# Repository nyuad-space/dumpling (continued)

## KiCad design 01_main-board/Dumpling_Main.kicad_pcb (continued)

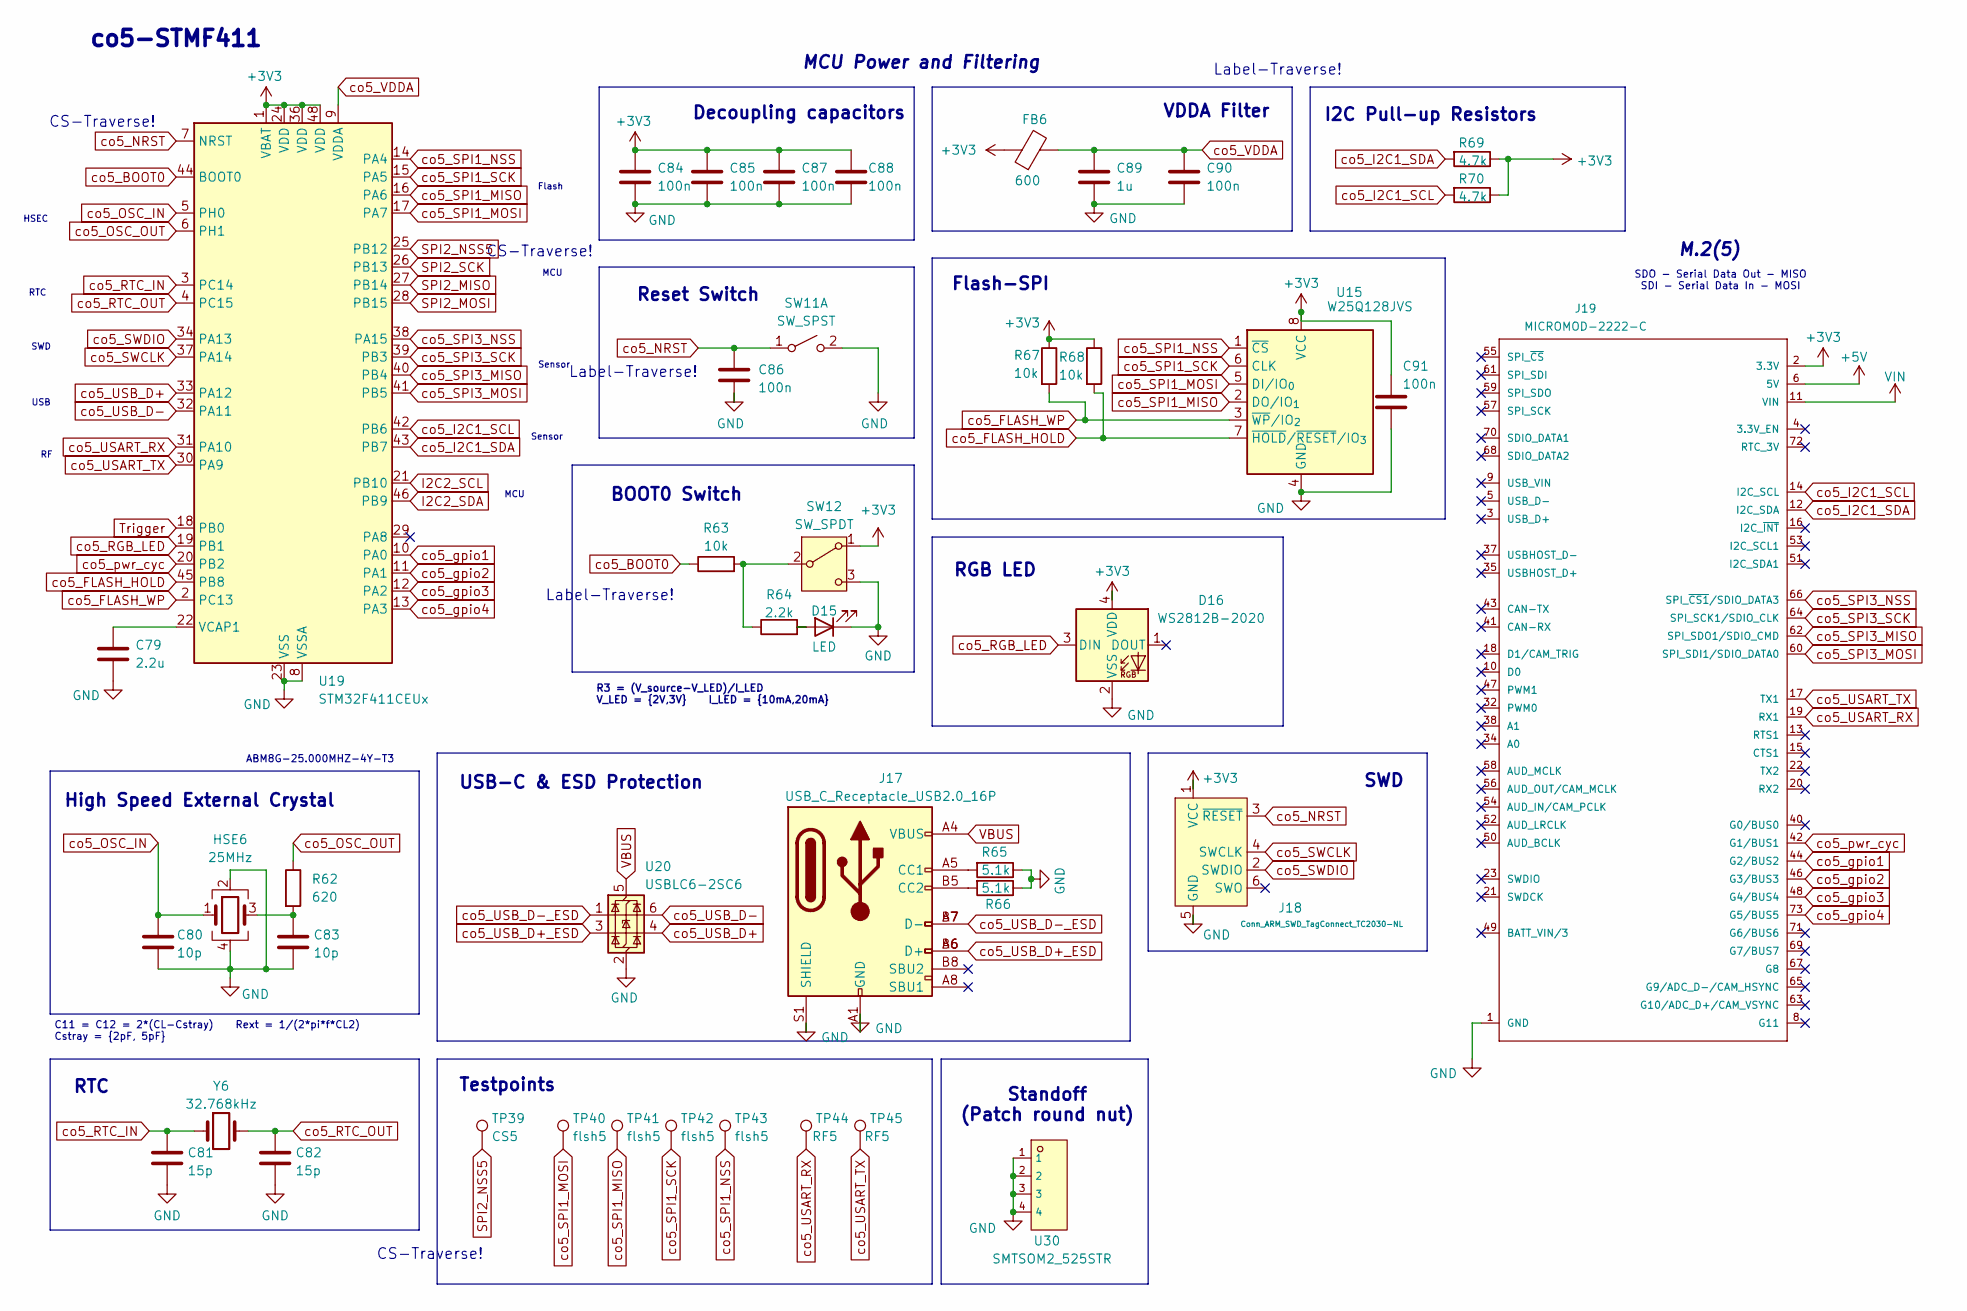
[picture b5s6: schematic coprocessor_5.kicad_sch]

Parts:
C79: 2.2u; C_0603_1608Metric
C80, C83: 10p; C_0402_1005Metric
C81, C82: 15p; C_0402_1005Metric
C84, C85, C86, C87, C88, C90, C91: 100n; C_0402_1005Metric
C89: 1u; C_0603_1608Metric
D15: LED; LED_0603_1608Metric
D16: WS2812B-2020; LED_WS2812B-2020_PLCC4_2.0x2.0mm
FB6: 600; L_0402_1005Metric
HSE6: 25MHz; Crystal_SMD_Abracon_ABM8G-4Pin_3.2x2.5mm
J17: USB_C_Receptacle_USB2.0_16P; USB_C_Receptacle_G-Switch_GT-USB-7051x
J18: Conn_ARM_SWD_TagConnect_TC2030-NL; Tag-Connect_TC2030-IDC-NL_2x03_P1.27mm_Vertical
J19: MICROMOD-2222-C; TE_2199119-4
R62: 620; R_0402_1005Metric
R63, R67, R68: 10k; R_0402_1005Metric
R64: 2.2k; R_0603_1608Metric
R65, R66: 5.1k; R_0402_1005Metric
R69, R70: 4.7k; R_0402_1005Metric
SW11: SW_SPST; SW_SPST_B3U-1000P
SW12: SW_SPDT; SW_JS102011JCQN
TP39: CS5; TestPoint_Pad_D1.0mm
TP40, TP41, TP42, TP43: flsh5; TestPoint_Pad_D1.0mm
TP44, TP45: RF5; TestPoint_Pad_D1.0mm
U15: W25Q128JVS; SOIC-8_5.3x5.3mm_P1.27mm
U19: STM32F411CEUx; QFN-48-1EP_7x7mm_P0.5mm_EP5.6x5.6mm
U20: USBLC6-2SC6; SOT-23-6
U30: SMTSOM2_525STR; SMD_BD5.6-D4.1; LCSC C22368605
Y6: 32.768kHz; Crystal_SMD_3215-2Pin_3.2x1.5mm

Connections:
+5V: J19.6 (5V); also elsewhere on the board
I2C2_SCL: U19.21 (PB10); also elsewhere on the board
I2C2_SDA: U19.46 (PB9); also elsewhere on the board
unnamed: C83.1, HSE6.3, R62.2
unnamed: D15.2 (A), R64.2
unnamed: J17.A5 (CC1), R65.2
unnamed: J17.B5 (CC2), R66.2
unnamed: R63.2, R64.1, SW12.2 (B)
unnamed: C79.1, U19.22 (VCAP1)
SPI2_MISO: U19.27 (PB14); also elsewhere on the board
SPI2_MOSI: U19.28 (PB15); also elsewhere on the board
SPI2_NSS5: TP39.1, U19.25 (PB12); also elsewhere on the board
SPI2_SCK: U19.26 (PB13); also elsewhere on the board
Trigger: U19.18 (PB0); also elsewhere on the board
VBUS: J17.A4 (VBUS), J17.A9 (VBUS), J17.B4 (VBUS), J17.B9 (VBUS), U20.5 (VBUS); also elsewhere on the board
VIN: J19.11 (VIN); also elsewhere on the board
co5_BOOT0: R63.1, U19.44 (BOOT0)
co5_FLASH_HOLD: R68.2, U15.7 (~HOLD/~RESET/IO_{3}), U19.45 (PB8)
co5_FLASH_WP: R67.2, U15.3 (~WP/IO_{2}), U19.2 (PC13)
co5_I2C1_SCL: J19.14 (I2C_SCL), R70.2, U19.42 (PB6)
co5_I2C1_SDA: J19.12 (I2C_SDA), R69.2, U19.43 (PB7)
co5_NRST: C86.1, J18.3 (~RESET), SW11.1 (A), U19.7 (NRST); also elsewhere on the board
co5_OSC_IN: C80.1, HSE6.1, U19.5 (PH0)
co5_OSC_OUT: R62.1, U19.6 (PH1)
co5_RGB_LED: D16.3 (DIN), U19.19 (PB1)
co5_RTC_IN: C81.1, U19.3 (PC14), Y6.1
co5_RTC_OUT: C82.1, U19.4 (PC15), Y6.2
co5_SPI1_MISO: TP41.1, U15.2 (DO/IO_{1}), U19.16 (PA6)
co5_SPI1_MOSI: TP40.1, U15.5 (DI/IO_{0}), U19.17 (PA7)
co5_SPI1_NSS: TP43.1, U15.1 (~CS), U19.14 (PA4)
co5_SPI1_SCK: TP42.1, U15.6 (CLK), U19.15 (PA5)
co5_SPI3_MISO: J19.62 (SPI_SDO1/SDIO_CMD), U19.40 (PB4)
co5_SPI3_MOSI: J19.60 (SPI_SDI1/SDIO_DATA0), U19.41 (PB5)
co5_SPI3_NSS: J19.66 (SPI_~CS1/SDIO_DATA3), U19.38 (PA15)
co5_SPI3_SCK: J19.64 (SPI_SCK1/SDIO_CLK), U19.39 (PB3)
co5_SWCLK: J18.4 (SWCLK), U19.37 (PA14)
co5_SWDIO: J18.2 (SWDIO), U19.34 (PA13)
co5_USART_RX: J19.19 (RX1), TP44.1, U19.31 (PA10)
co5_USART_TX: J19.17 (TX1), TP45.1, U19.30 (PA9)
co5_USB_D+: U19.33 (PA12), U20.4 (I/O2)
co5_USB_D+_ESD: J17.A6 (D+), J17.B6 (D+), U20.3 (I/O2)
co5_USB_D-: U19.32 (PA11), U20.6 (I/O1)
co5_USB_D-_ESD: J17.A7 (D-), J17.B7 (D-), U20.1 (I/O1)
co5_VDDA: C89.1, C90.1, FB6.2, U19.9 (VDDA)
co5_gpio1: J19.44 (G2/BUS2), U19.10 (PA0)
co5_gpio2: J19.46 (G3/BUS3), U19.11 (PA1)
co5_gpio3: J19.48 (G4/BUS4), U19.12 (PA2)
co5_gpio4: J19.73 (G5/BUS5), U19.13 (PA3)
co5_pwr_cyc: J19.42 (G1/BUS1), U19.20 (PB2)

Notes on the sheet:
USB
Flash
Reset Switch
M.2(5)
Testpoints
BOOT0 Switch
R3 = (V_source-V_LED)/I_LED V_LED = {2V,3V} I_LED = {10mA,20mA}
SDO - Serial Data Out - MISO SDI - Serial Data In - MOSI
RTC
Sensor
CS-Traverse!
MCU Power and Filtering
MCU
ABM8G-25.000MHZ-4Y-T3
SWD
RGB LED
Flash-SPI
co5-STMF411
Standoff (Patch round nut)
SWD
I2C Pull-up Resistors
Label-Traverse!
VDDA Filter
RTC
C11 = C12 = 2*(CL-Cstray) Rext = 1/(2*pi*f*CL2) Cstray = {2pF, 5pF}
High Speed External Crystal
Decoupling capacitors
USB-C & ESD Protection
HSEC

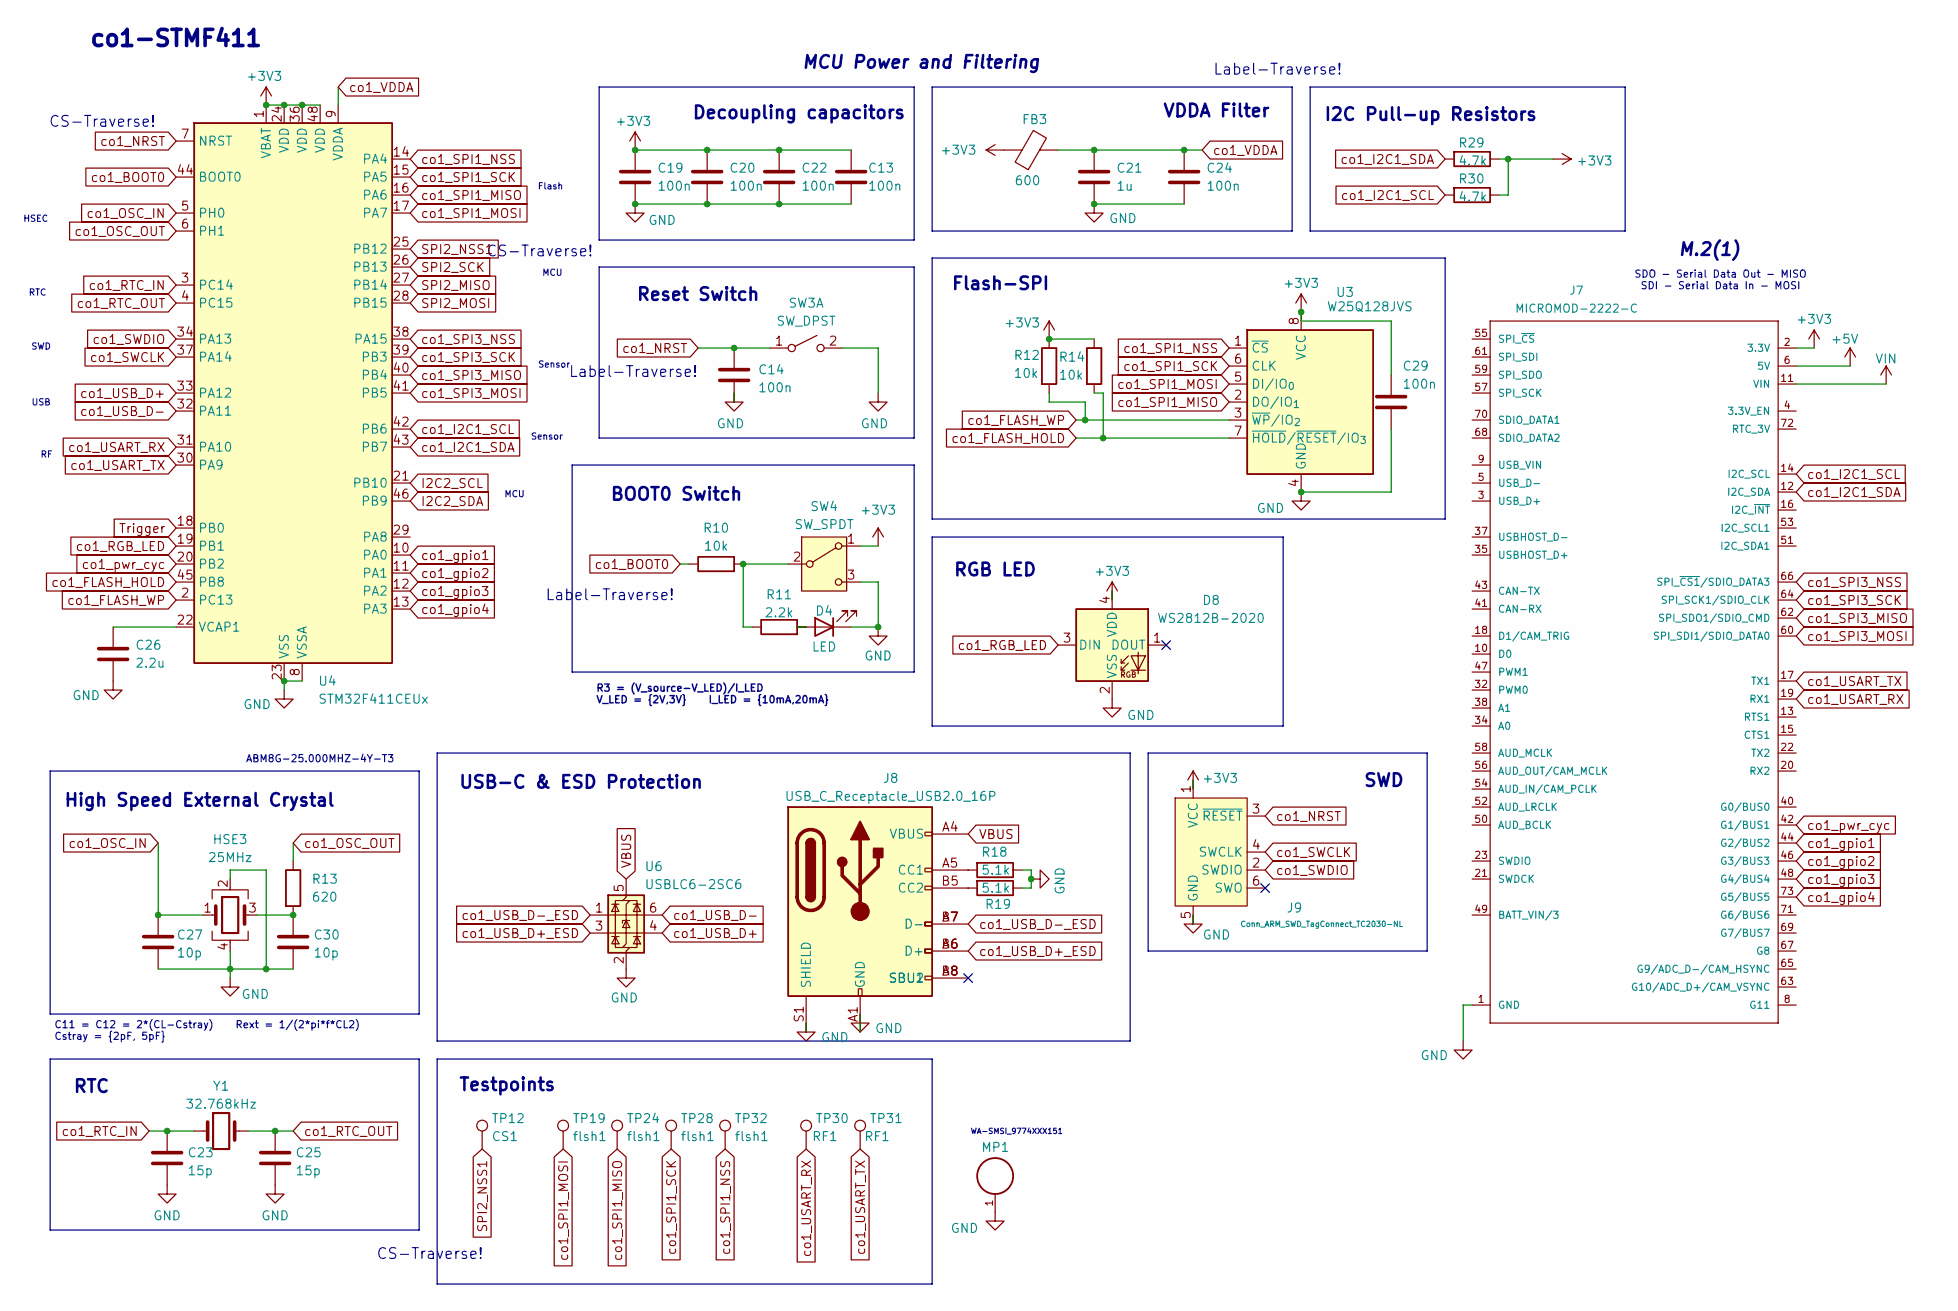
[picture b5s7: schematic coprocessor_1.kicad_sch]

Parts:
C13, C14, C19, C20, C22, C24, C29: 100n; C_0402_1005Metric
C21: 1u; C_0603_1608Metric
C23, C25: 15p; C_0402_1005Metric
C26: 2.2u; C_0603_1608Metric
C27, C30: 10p; C_0402_1005Metric
D4: LED; LED_0603_1608Metric
D8: WS2812B-2020; LED_WS2812B-2020_PLCC4_2.0x2.0mm
FB3: 600; L_0402_1005Metric
HSE3: 25MHz; Crystal_SMD_Abracon_ABM8G-4Pin_3.2x2.5mm
J7: MICROMOD-2222-C; TE_2199119-4
J8: USB_C_Receptacle_USB2.0_16P; USB_C_Receptacle_G-Switch_GT-USB-7051x
J9: Conn_ARM_SWD_TagConnect_TC2030-NL; Tag-Connect_TC2030-IDC-NL_2x03_P1.27mm_Vertical
MP1: WA-SMSI_9774025151; PART-NUMBER 9774025151R
R10, R12, R14: 10k; R_0402_1005Metric
R11: 2.2k; R_0603_1608Metric
R13: 620; R_0402_1005Metric
R18, R19: 5.1k; R_0402_1005Metric
R29, R30: 4.7k; R_0402_1005Metric
SW3: SW_DPST; SW_SPST_B3U-1000P
SW4: SW_SPDT; SW_CJS-1200TA
TP12: CS1; TestPoint_Pad_D1.0mm
TP19, TP24, TP28, TP32: flsh1; TestPoint_Pad_D1.0mm
TP30, TP31: RF1; TestPoint_Pad_D1.0mm
U3: W25Q128JVS; SOIC-8_5.3x5.3mm_P1.27mm
U4: STM32F411CEUx; QFN-48-1EP_7x7mm_P0.5mm_EP5.6x5.6mm
U6: USBLC6-2SC6; SOT-23-6
Y1: 32.768kHz; Crystal_SMD_3215-2Pin_3.2x1.5mm

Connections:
+5V: J7.6 (5V); also elsewhere on the board
I2C2_SCL: U4.21 (PB10); also elsewhere on the board
I2C2_SDA: U4.46 (PB9); also elsewhere on the board
unnamed: C30.1, HSE3.3, R13.2
unnamed: D4.2 (A), R11.2
unnamed: J8.A5 (CC1), R18.2
unnamed: J8.B5 (CC2), R19.2
unnamed: R10.2, R11.1, SW4.2 (B)
unnamed: C26.1, U4.22 (VCAP1)
SPI2_MISO: U4.27 (PB14); also elsewhere on the board
SPI2_MOSI: U4.28 (PB15); also elsewhere on the board
SPI2_NSS1: TP12.1, U4.25 (PB12); also elsewhere on the board
SPI2_SCK: U4.26 (PB13); also elsewhere on the board
Trigger: U4.18 (PB0); also elsewhere on the board
VBUS: J8.A4 (VBUS), J8.A9 (VBUS), J8.B4 (VBUS), J8.B9 (VBUS), U6.5 (VBUS); also elsewhere on the board
VIN: J7.11 (VIN); also elsewhere on the board
co1_BOOT0: R10.1, U4.44 (BOOT0)
co1_FLASH_HOLD: R14.2, U3.7 (~HOLD/~RESET/IO_{3}), U4.45 (PB8)
co1_FLASH_WP: R12.2, U3.3 (~WP/IO_{2}), U4.2 (PC13)
co1_I2C1_SCL: J7.14 (I2C_SCL), R30.2, U4.42 (PB6)
co1_I2C1_SDA: J7.12 (I2C_SDA), R29.2, U4.43 (PB7)
co1_NRST: C14.1, J9.3 (~RESET), SW3.1 (A), U4.7 (NRST); also elsewhere on the board
co1_OSC_IN: C27.1, HSE3.1, U4.5 (PH0)
co1_OSC_OUT: R13.1, U4.6 (PH1)
co1_RGB_LED: D8.3 (DIN), U4.19 (PB1)
co1_RTC_IN: C23.1, U4.3 (PC14), Y1.1
co1_RTC_OUT: C25.1, U4.4 (PC15), Y1.2
co1_SPI1_MISO: TP24.1, U3.2 (DO/IO_{1}), U4.16 (PA6)
co1_SPI1_MOSI: TP19.1, U3.5 (DI/IO_{0}), U4.17 (PA7)
co1_SPI1_NSS: TP32.1, U3.1 (~CS), U4.14 (PA4)
co1_SPI1_SCK: TP28.1, U3.6 (CLK), U4.15 (PA5)
co1_SPI3_MISO: J7.62 (SPI_SDO1/SDIO_CMD), U4.40 (PB4)
co1_SPI3_MOSI: J7.60 (SPI_SDI1/SDIO_DATA0), U4.41 (PB5)
co1_SPI3_NSS: J7.66 (SPI_~CS1/SDIO_DATA3), U4.38 (PA15)
co1_SPI3_SCK: J7.64 (SPI_SCK1/SDIO_CLK), U4.39 (PB3)
co1_SWCLK: J9.4 (SWCLK), U4.37 (PA14)
co1_SWDIO: J9.2 (SWDIO), U4.34 (PA13)
co1_USART_RX: J7.19 (RX1), TP30.1, U4.31 (PA10)
co1_USART_TX: J7.17 (TX1), TP31.1, U4.30 (PA9)
co1_USB_D+: U4.33 (PA12), U6.4 (I/O2)
co1_USB_D+_ESD: J8.A6 (D+), J8.B6 (D+), U6.3 (I/O2)
co1_USB_D-: U4.32 (PA11), U6.6 (I/O1)
co1_USB_D-_ESD: J8.A7 (D-), J8.B7 (D-), U6.1 (I/O1)
co1_VDDA: C21.1, C24.1, FB3.2, U4.9 (VDDA)
co1_gpio1: J7.44 (G2/BUS2), U4.10 (PA0)
co1_gpio2: J7.46 (G3/BUS3), U4.11 (PA1)
co1_gpio3: J7.48 (G4/BUS4), U4.12 (PA2)
co1_gpio4: J7.73 (G5/BUS5), U4.13 (PA3)
co1_pwr_cyc: J7.42 (G1/BUS1), U4.20 (PB2)

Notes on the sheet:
WA-SMSI_9774XXX151
Flash-SPI
VDDA Filter
I2C Pull-up Resistors
SDO - Serial Data Out - MISO SDI - Serial Data In - MOSI
Sensor
HSEC
ABM8G-25.000MHZ-4Y-T3
Testpoints
CS-Traverse!
RGB LED
M.2(1)
RTC
SWD
C11 = C12 = 2*(CL-Cstray) Rext = 1/(2*pi*f*CL2) Cstray = {2pF, 5pF}
RTC
co1-STMF411
USB
Reset Switch
Label-Traverse!
Flash
Decoupling capacitors
SWD
MCU
BOOT0 Switch
MCU Power and Filtering
R3 = (V_source-V_LED)/I_LED V_LED = {2V,3V} I_LED = {10mA,20mA}
USB-C & ESD Protection
High Speed External Crystal

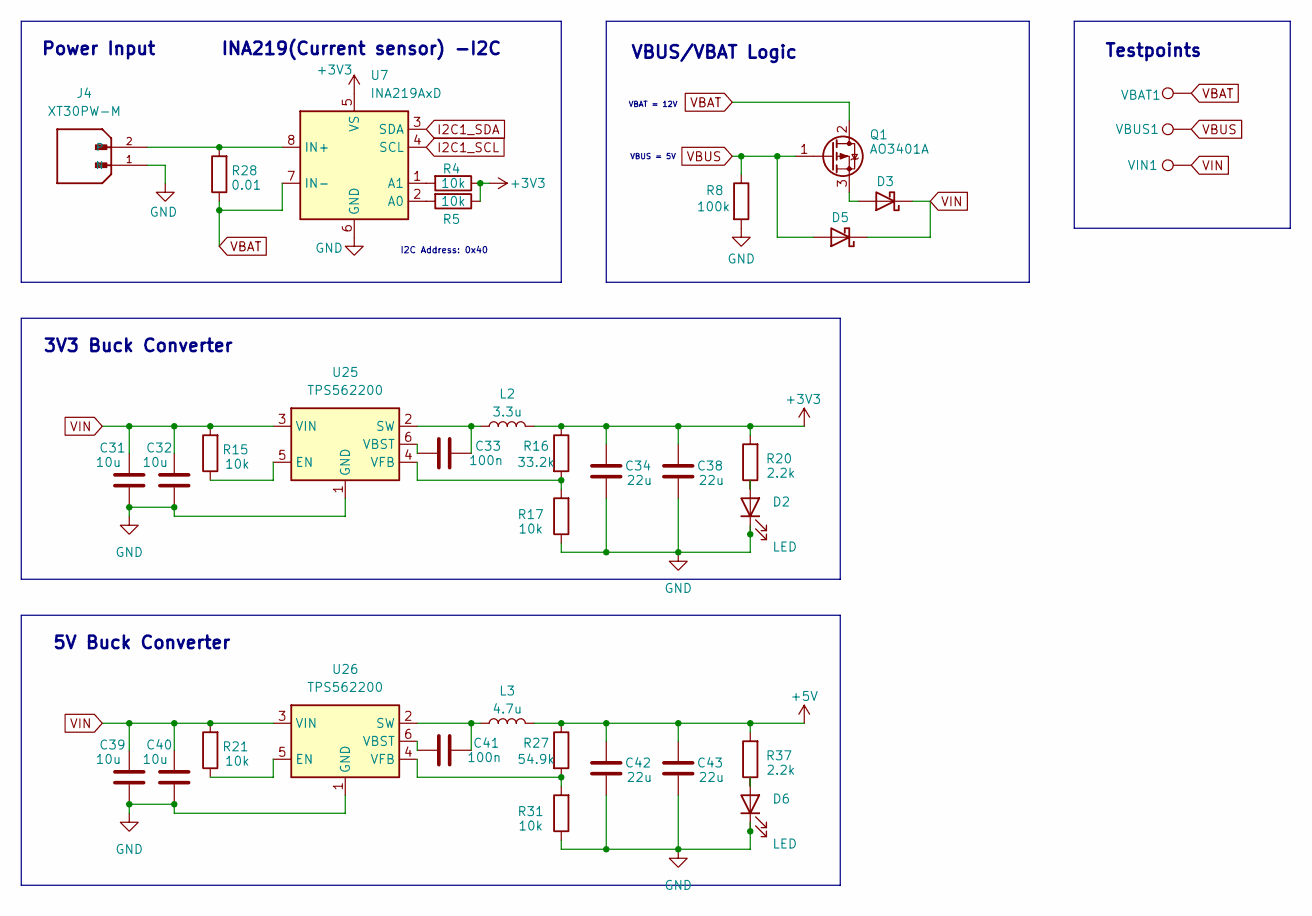
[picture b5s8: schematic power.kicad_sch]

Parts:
C31, C32, C39, C40: 10u; C_0805_2012Metric
C33, C41: 100n; C_0402_1005Metric
C34, C38, C42, C43: 22u; C_0805_2012Metric
D2, D6: LED; LED_0603_1608Metric
D3, D5: D_Schottky; D_SOD-323
J4: XT30PW-M; AMASS_XT30PW-M_1x02_P2.50mm_Horizontal; PARTREV 1.2
L2: 3.3u; L_Changjiang_FNR4030S
L3: 4.7u; L_Changjiang_FNR4030S
Q1: AO3401A; SOT-23
R4, R5, R15, R17, R21, R31: 10k; R_0402_1005Metric
R8: 100k; R_0603_1608Metric
R16: 33.2k; R_0402_1005Metric
R20, R37: 2.2k; R_0603_1608Metric
R27: 54.9k; R_0402_1005Metric
R28: 0.01; R_2512_6332Metric
U7: INA219AxD; SOIC-8_3.9x4.9mm_P1.27mm
U25, U26: TPS562200; SOT-23-6_Handsoldering
VBAT1: TestPoint; TestPoint_Pad_D1.5mm
VBUS1: TestPoint; TestPoint_Pad_D1.5mm
VIN1: TestPoint; TestPoint_Pad_D1.5mm

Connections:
+5V: C42.1, C43.1, L3.2, R27.1, R37.2; also elsewhere on the board
unnamed: D2.2 (A), R20.1
unnamed: D3.2 (A), Q1.3 (S)
unnamed: D6.2 (A), R37.1
unnamed 58: R5.2, U7.2 (A0); also elsewhere on the board
unnamed: R15.1, U25.5 (EN)
unnamed: C33.2, L2.1, U25.2 (SW)
unnamed: C33.1, U25.6 (VBST)
unnamed: R16.2, R17.2, U25.4 (VFB)
unnamed: R21.1, U26.5 (EN)
unnamed: C41.2, L3.1, U26.2 (SW)
unnamed: C41.1, U26.6 (VBST)
unnamed: R27.2, R31.2, U26.4 (VFB)
VBUS: D5.2 (A), Q1.1 (G), R8.1, VBUS1.1; also elsewhere on the board
VIN: C31.1, C32.1, C39.1, C40.1, D3.1 (K), D5.1 (K), R15.2, R21.2, U25.3 (VIN), U26.3 (VIN), VIN1.1; also elsewhere on the board

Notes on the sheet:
3V3 Buck Converter
VBAT = 12V
Testpoints
Power Input
5V Buck Converter
INA219(Current sensor) -I2C
VBUS/VBAT Logic
I2C Address: 0x40
VBUS = 5V

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
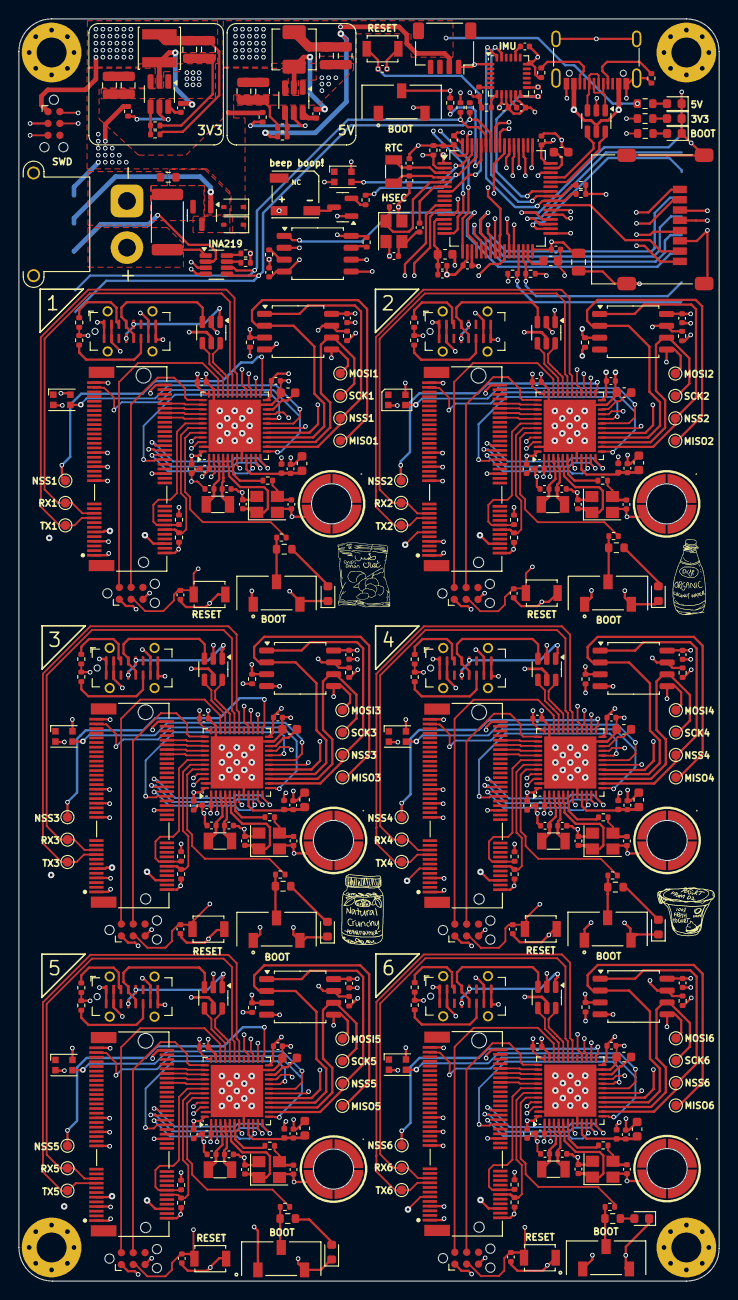
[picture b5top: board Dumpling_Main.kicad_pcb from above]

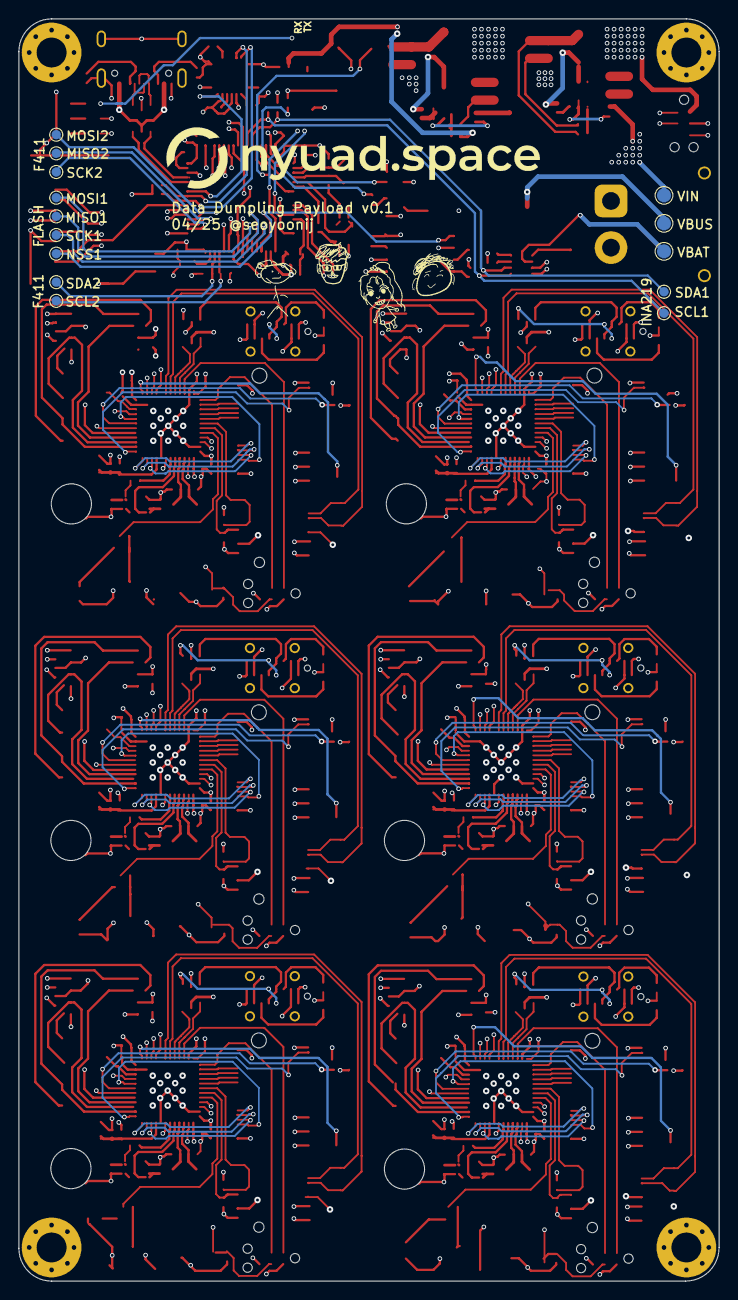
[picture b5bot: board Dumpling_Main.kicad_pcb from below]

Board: 6 copper layers, 75.0 x 135.2 mm, 363 parts (14 on the bottom side), 313 nets.

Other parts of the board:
U9: INA219AxDCN; SOT-23-8
U21, U29: SMTSOM2_525STR; SMD_BD5.6-D4.1

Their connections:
I2C1_SCL: U9.5 (SCL); also elsewhere on the board
I2C1_SDA: U9.6 (SDA); also elsewhere on the board
unnamed 58: U9.7 (A0); also elsewhere on the board

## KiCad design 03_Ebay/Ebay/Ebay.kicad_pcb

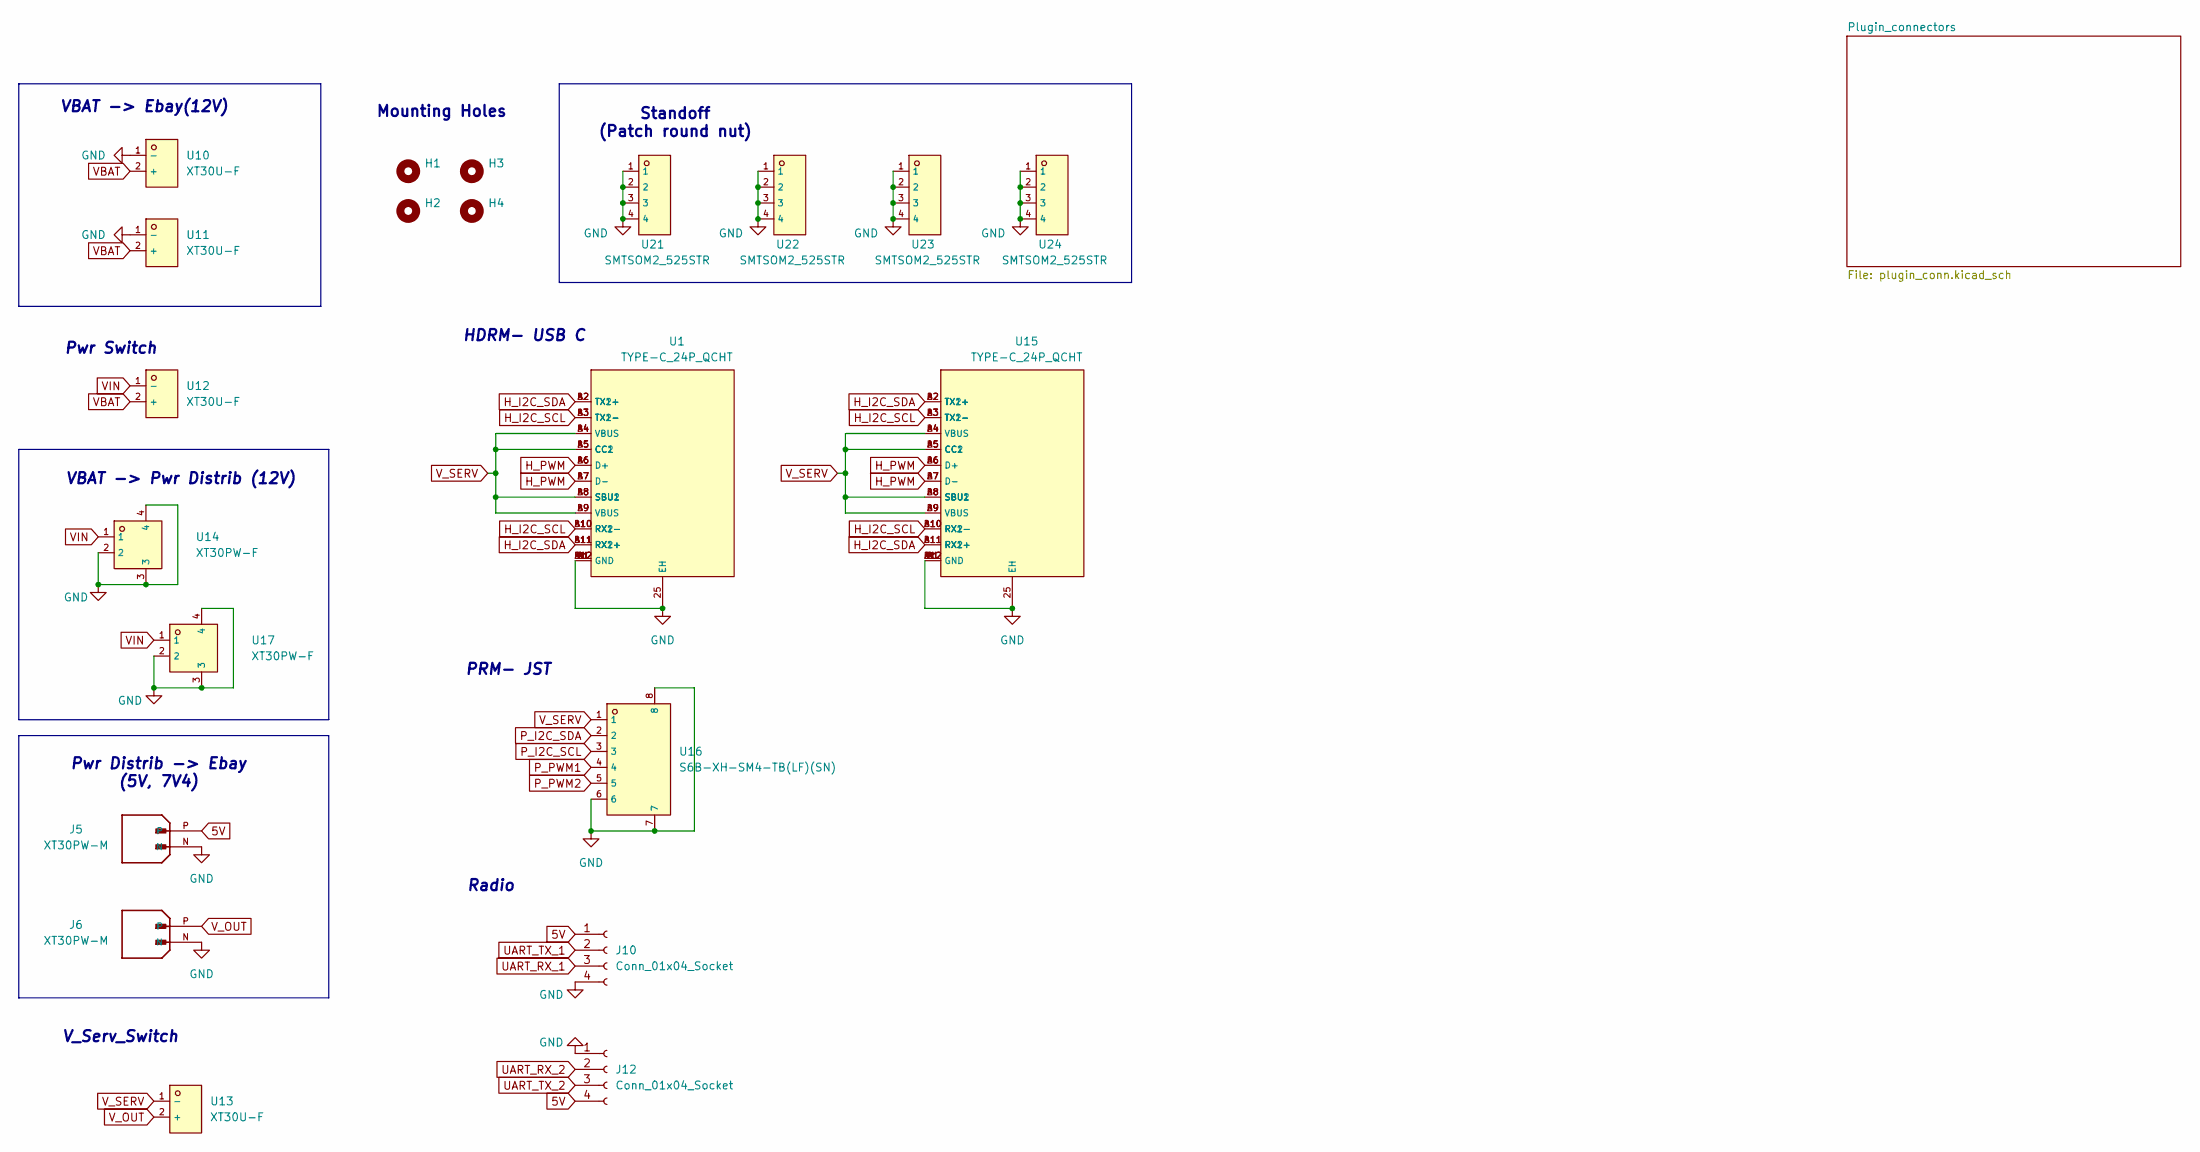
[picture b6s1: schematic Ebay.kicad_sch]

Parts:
H1, H2, H3, H4: MountingHole; MountingHole_3.2mm_M3_Pad_Via
J5, J6: XT30PW-M; AMASS_XT30PW-M; PARTREV 1.2
J10, J12: Conn_01x04_Socket; PinHeader_1x04_P2.54mm_Horizontal
U1, U15: TYPE-C_24P_QCHT; TYPE-C-SMD_TYPE-C-24P-QCHT; LCSC C456013
U10, U11, U12, U13: XT30U-F; CONN-TH_XT30U-F; LCSC C99102
U14, U17: XT30PW-F; CONN-TH_XT30PW-F-1; LCSC C2913282
U16: S6B-XH-SM4-TB(LF)(SN); CONN-SMD_S6B-XH-SM4-TB-LF-SN; LCSC C191914
U21, U22, U23, U24: SMTSOM2_525STR; SMD_BD5.6-D4.1; LCSC C22368605

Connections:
5V: J5.P, J10.1, J12.4; also elsewhere on the board
GND: J5.N, J6.N, J10.4, J12.1, U1.25 (EH), U1.A1 (GND), U1.A12 (GND), U1.B1 (GND), U1.B12 (GND), U10.1 (-), U11.1 (-), U14.2, U14.3, U14.4, U15.25 (EH), U15.A1 (GND), U15.A12 (GND), U15.B1 (GND), U15.B12 (GND), U16.6, U16.7, U16.8, U17.2, U17.3, U17.4, U21.1, U21.2, U21.3, U21.4, U22.1, U22.2, U22.3, U22.4, U23.1, U23.2, U23.3, U23.4, U24.1, U24.2, U24.3, U24.4; also elsewhere on the board
H_I2C_SCL: U1.A3 (TX1-), U1.A10 (RX2-), U1.B3 (TX2-), U1.B10 (RX1-), U15.A3 (TX1-), U15.A10 (RX2-), U15.B3 (TX2-), U15.B10 (RX1-); also elsewhere on the board
H_I2C_SDA: U1.A2 (TX1+), U1.A11 (RX2+), U1.B2 (TX2+), U1.B11 (RX1+), U15.A2 (TX1+), U15.A11 (RX2+), U15.B2 (TX2+), U15.B11 (RX1+); also elsewhere on the board
H_PWM: U1.A6 (D+), U1.A7 (D-), U1.B6 (D+), U1.B7 (D-), U15.A6 (D+), U15.A7 (D-), U15.B6 (D+), U15.B7 (D-); also elsewhere on the board
P_I2C_SCL: U16.3; also elsewhere on the board
P_I2C_SDA: U16.2; also elsewhere on the board
P_PWM1: U16.4; also elsewhere on the board
P_PWM2: U16.5; also elsewhere on the board
UART_RX_1: J10.3; also elsewhere on the board
UART_RX_2: J12.2; also elsewhere on the board
UART_TX_1: J10.2; also elsewhere on the board
UART_TX_2: J12.3; also elsewhere on the board
VBAT: U10.2 (+), U11.2 (+), U12.2 (+)
VIN: U12.1 (-), U14.1, U17.1
V_OUT: J6.P, U13.2 (+)

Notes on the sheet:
PRM- JST
VBAT -> Pwr Distrib (12V)
Pwr Switch
Radio
Pwr Distrib -> Ebay (5V, 7V4)
VBAT -> Ebay(12V)
V_Serv_Switch
Standoff (Patch round nut)
Mounting Holes
HDRM- USB C

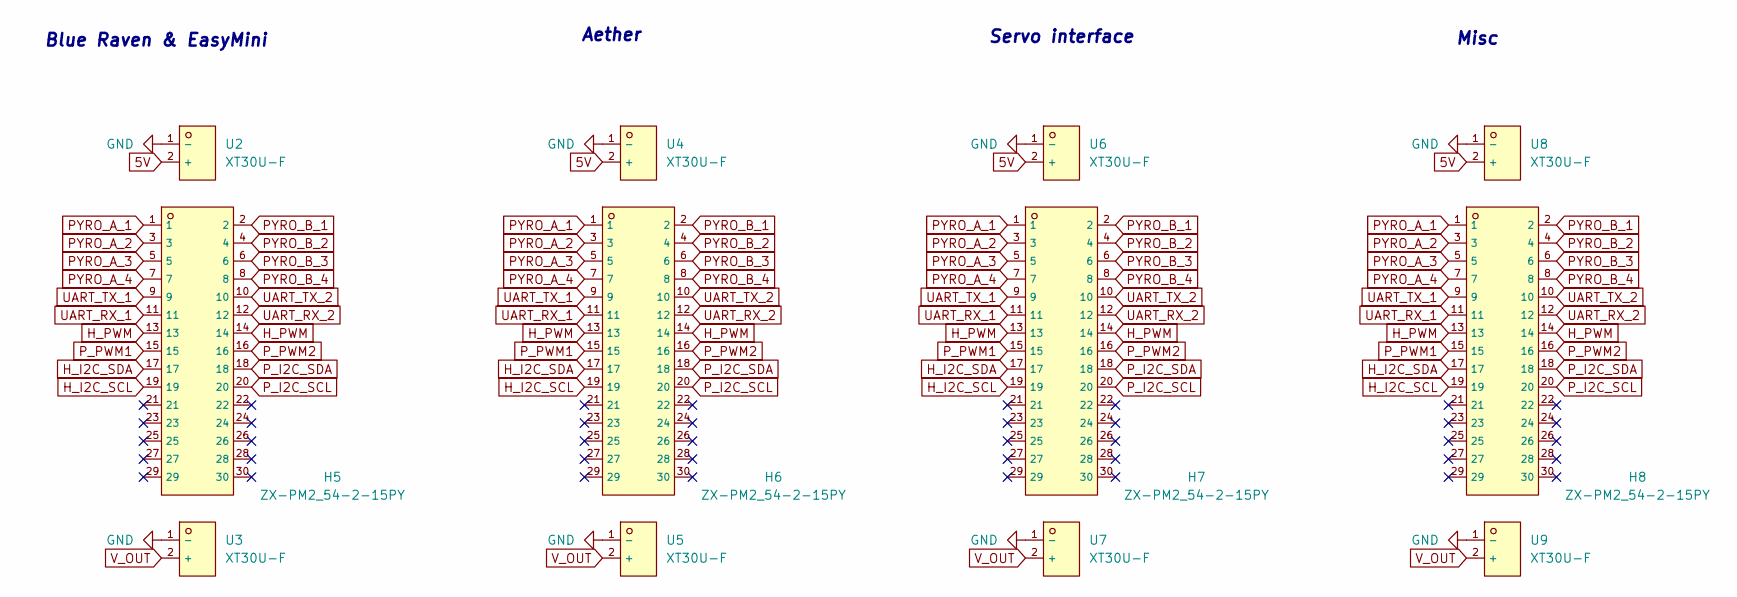
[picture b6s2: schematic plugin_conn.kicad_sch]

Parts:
H5, H6, H7, H8: ZX-PM2_54-2-15PY; PinSocket_2x15_P2.54mm_Vertical; LCSC C7499350
U2, U3, U4, U5, U6, U7, U8, U9: XT30U-F; CONN-TH_XT30U-F; LCSC C99102

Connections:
5V: U2.2 (+), U4.2 (+), U6.2 (+), U8.2 (+); also elsewhere on the board
GND: U2.1 (-), U3.1 (-), U4.1 (-), U5.1 (-), U6.1 (-), U7.1 (-), U8.1 (-), U9.1 (-); also elsewhere on the board
H_I2C_SCL: H5.19, H6.19, H7.19, H8.19; also elsewhere on the board
H_I2C_SDA: H5.17, H6.17, H7.17, H8.17; also elsewhere on the board
H_PWM: H5.13, H5.14, H6.13, H6.14, H7.13, H7.14, H8.13, H8.14; also elsewhere on the board
PYRO_A_1: H5.1, H6.1, H7.1, H8.1
PYRO_A_2: H5.3, H6.3, H7.3, H8.3
PYRO_A_3: H5.5, H6.5, H7.5, H8.5
PYRO_A_4: H5.7, H6.7, H7.7, H8.7
PYRO_B_1: H5.2, H6.2, H7.2, H8.2
PYRO_B_2: H5.4, H6.4, H7.4, H8.4
PYRO_B_3: H5.6, H6.6, H7.6, H8.6
PYRO_B_4: H5.8, H6.8, H7.8, H8.8
P_I2C_SCL: H5.20, H6.20, H7.20, H8.20; also elsewhere on the board
P_I2C_SDA: H5.18, H6.18, H7.18, H8.18; also elsewhere on the board
P_PWM1: H5.15, H6.15, H7.15, H8.15; also elsewhere on the board
P_PWM2: H5.16, H6.16, H7.16, H8.16; also elsewhere on the board
UART_RX_1: H5.11, H6.11, H7.11, H8.11; also elsewhere on the board
UART_RX_2: H5.12, H6.12, H7.12, H8.12; also elsewhere on the board
UART_TX_1: H5.9, H6.9, H7.9, H8.9; also elsewhere on the board
UART_TX_2: H5.10, H6.10, H7.10, H8.10; also elsewhere on the board

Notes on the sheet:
Servo interface
Misc
Blue Raven & EasyMini
Aether

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
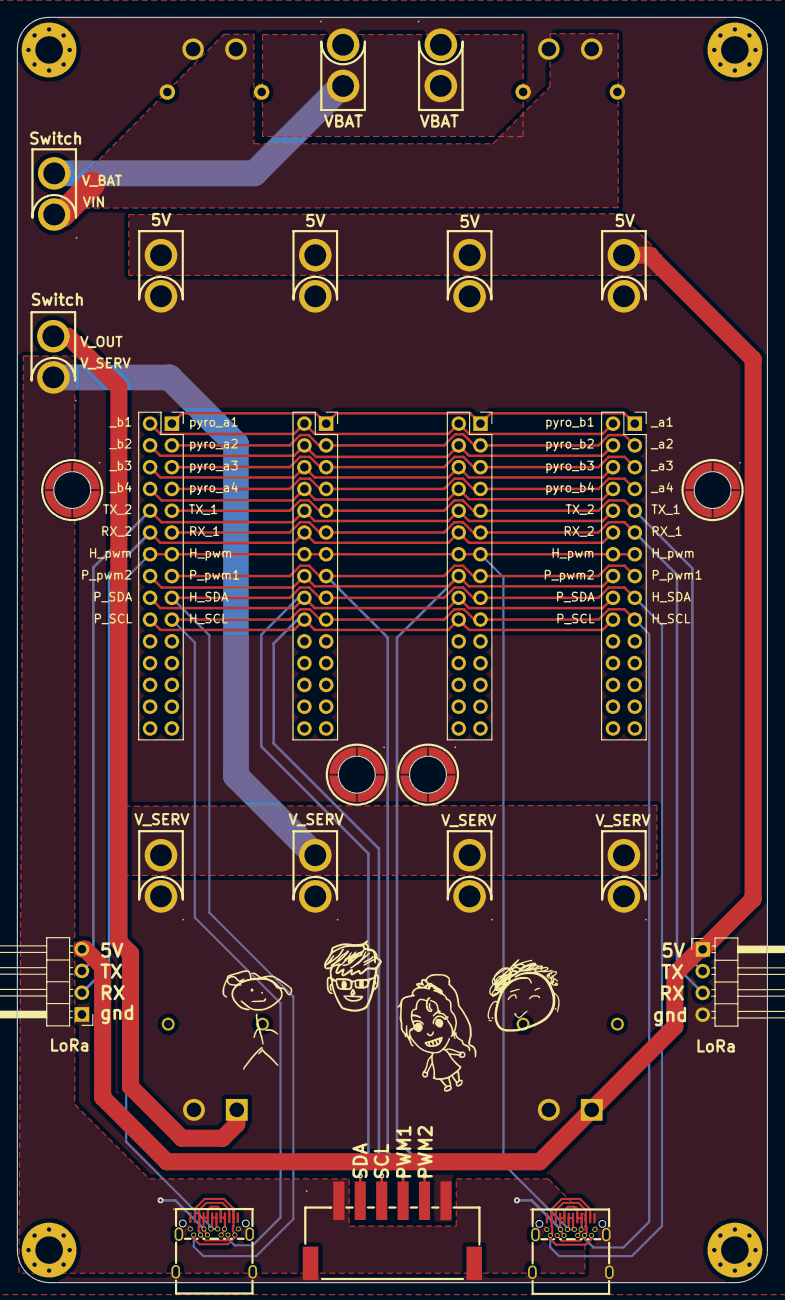
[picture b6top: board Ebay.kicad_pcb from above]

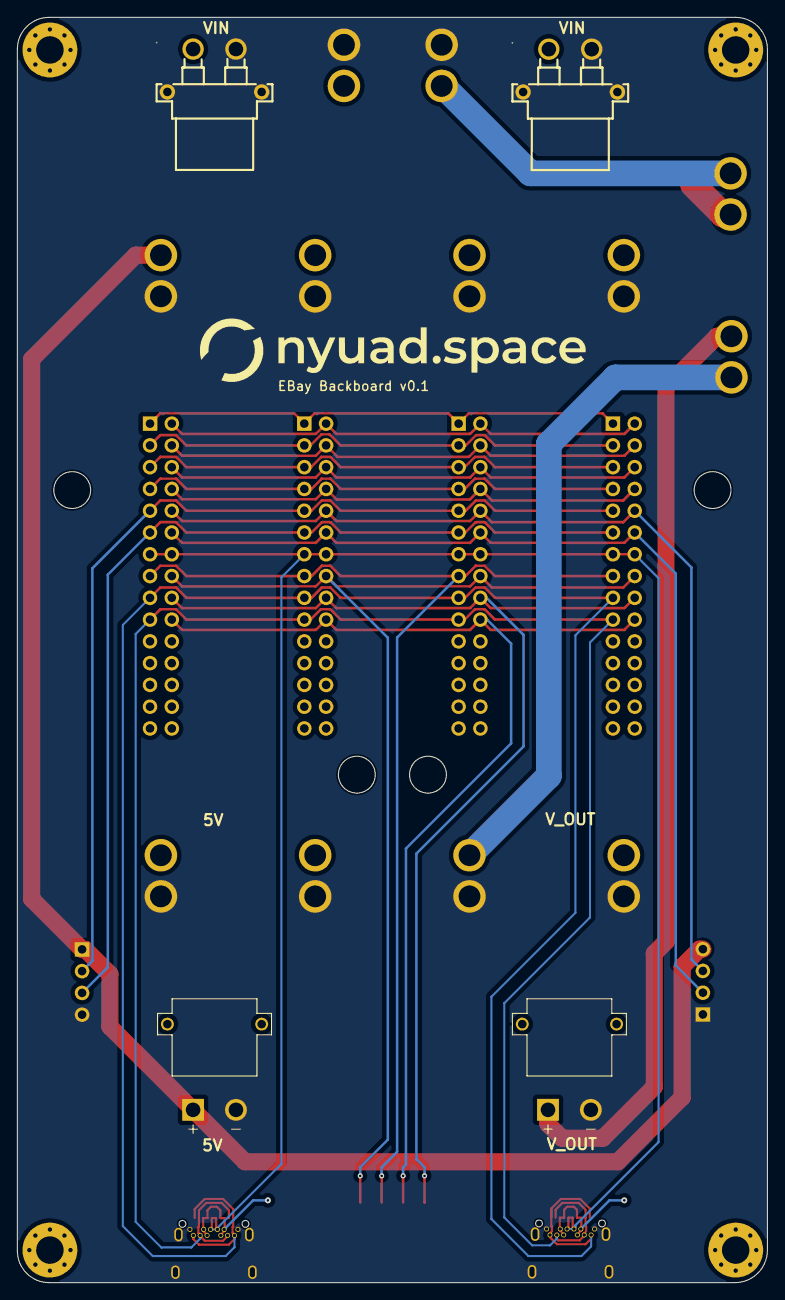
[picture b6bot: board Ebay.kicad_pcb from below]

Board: 2 copper layers, 87.5 x 147.6 mm, 33 parts (4 on the bottom side), 25 nets.
